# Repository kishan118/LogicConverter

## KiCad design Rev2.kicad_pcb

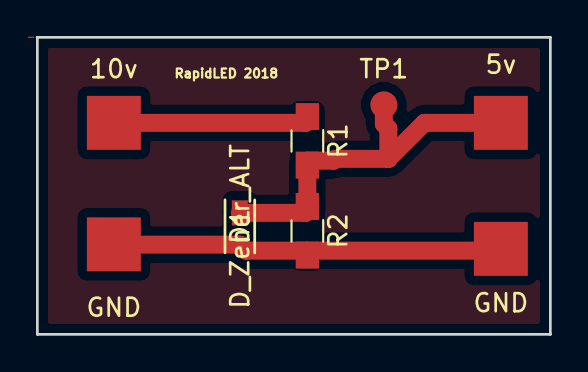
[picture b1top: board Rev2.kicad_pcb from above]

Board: 2 copper layers, 28.5 x 16.5 mm, 8 parts (0 on the bottom side), 3 nets.

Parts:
5v, 10v: TEST; Measurement_Point_Square-SMD-Pad_Big
D1: D_Zener_ALT; MSP5.0A-M3_89A
GND: TEST; Measurement_Point_Square-SMD-Pad_Big
GND#2: TEST; Measurement_Point_Square-SMD-Pad_Big
R1, R2: 10K; R_0805_HandSoldering
TP1: Measurement_Point_Round-SMD-Pad_Small

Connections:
GND: D1.2, GND.1, GND#2.1, R2.2
unnamed: 5v.1, D1.1, R1.2, R2.1, TP1.1
unnamed: 10v.1, R1.1

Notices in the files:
parts and their libraries:
Copyright 2016 Accelerated Designs. All rights reserved.
